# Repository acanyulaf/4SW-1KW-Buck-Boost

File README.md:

# 4SW-1KW-Buck-Boost
 1kW 28V 4 Switches Buck Boost Converter with 28V Fixed Output, Voltage Ripple<1% Inductor Current Ripple<30%

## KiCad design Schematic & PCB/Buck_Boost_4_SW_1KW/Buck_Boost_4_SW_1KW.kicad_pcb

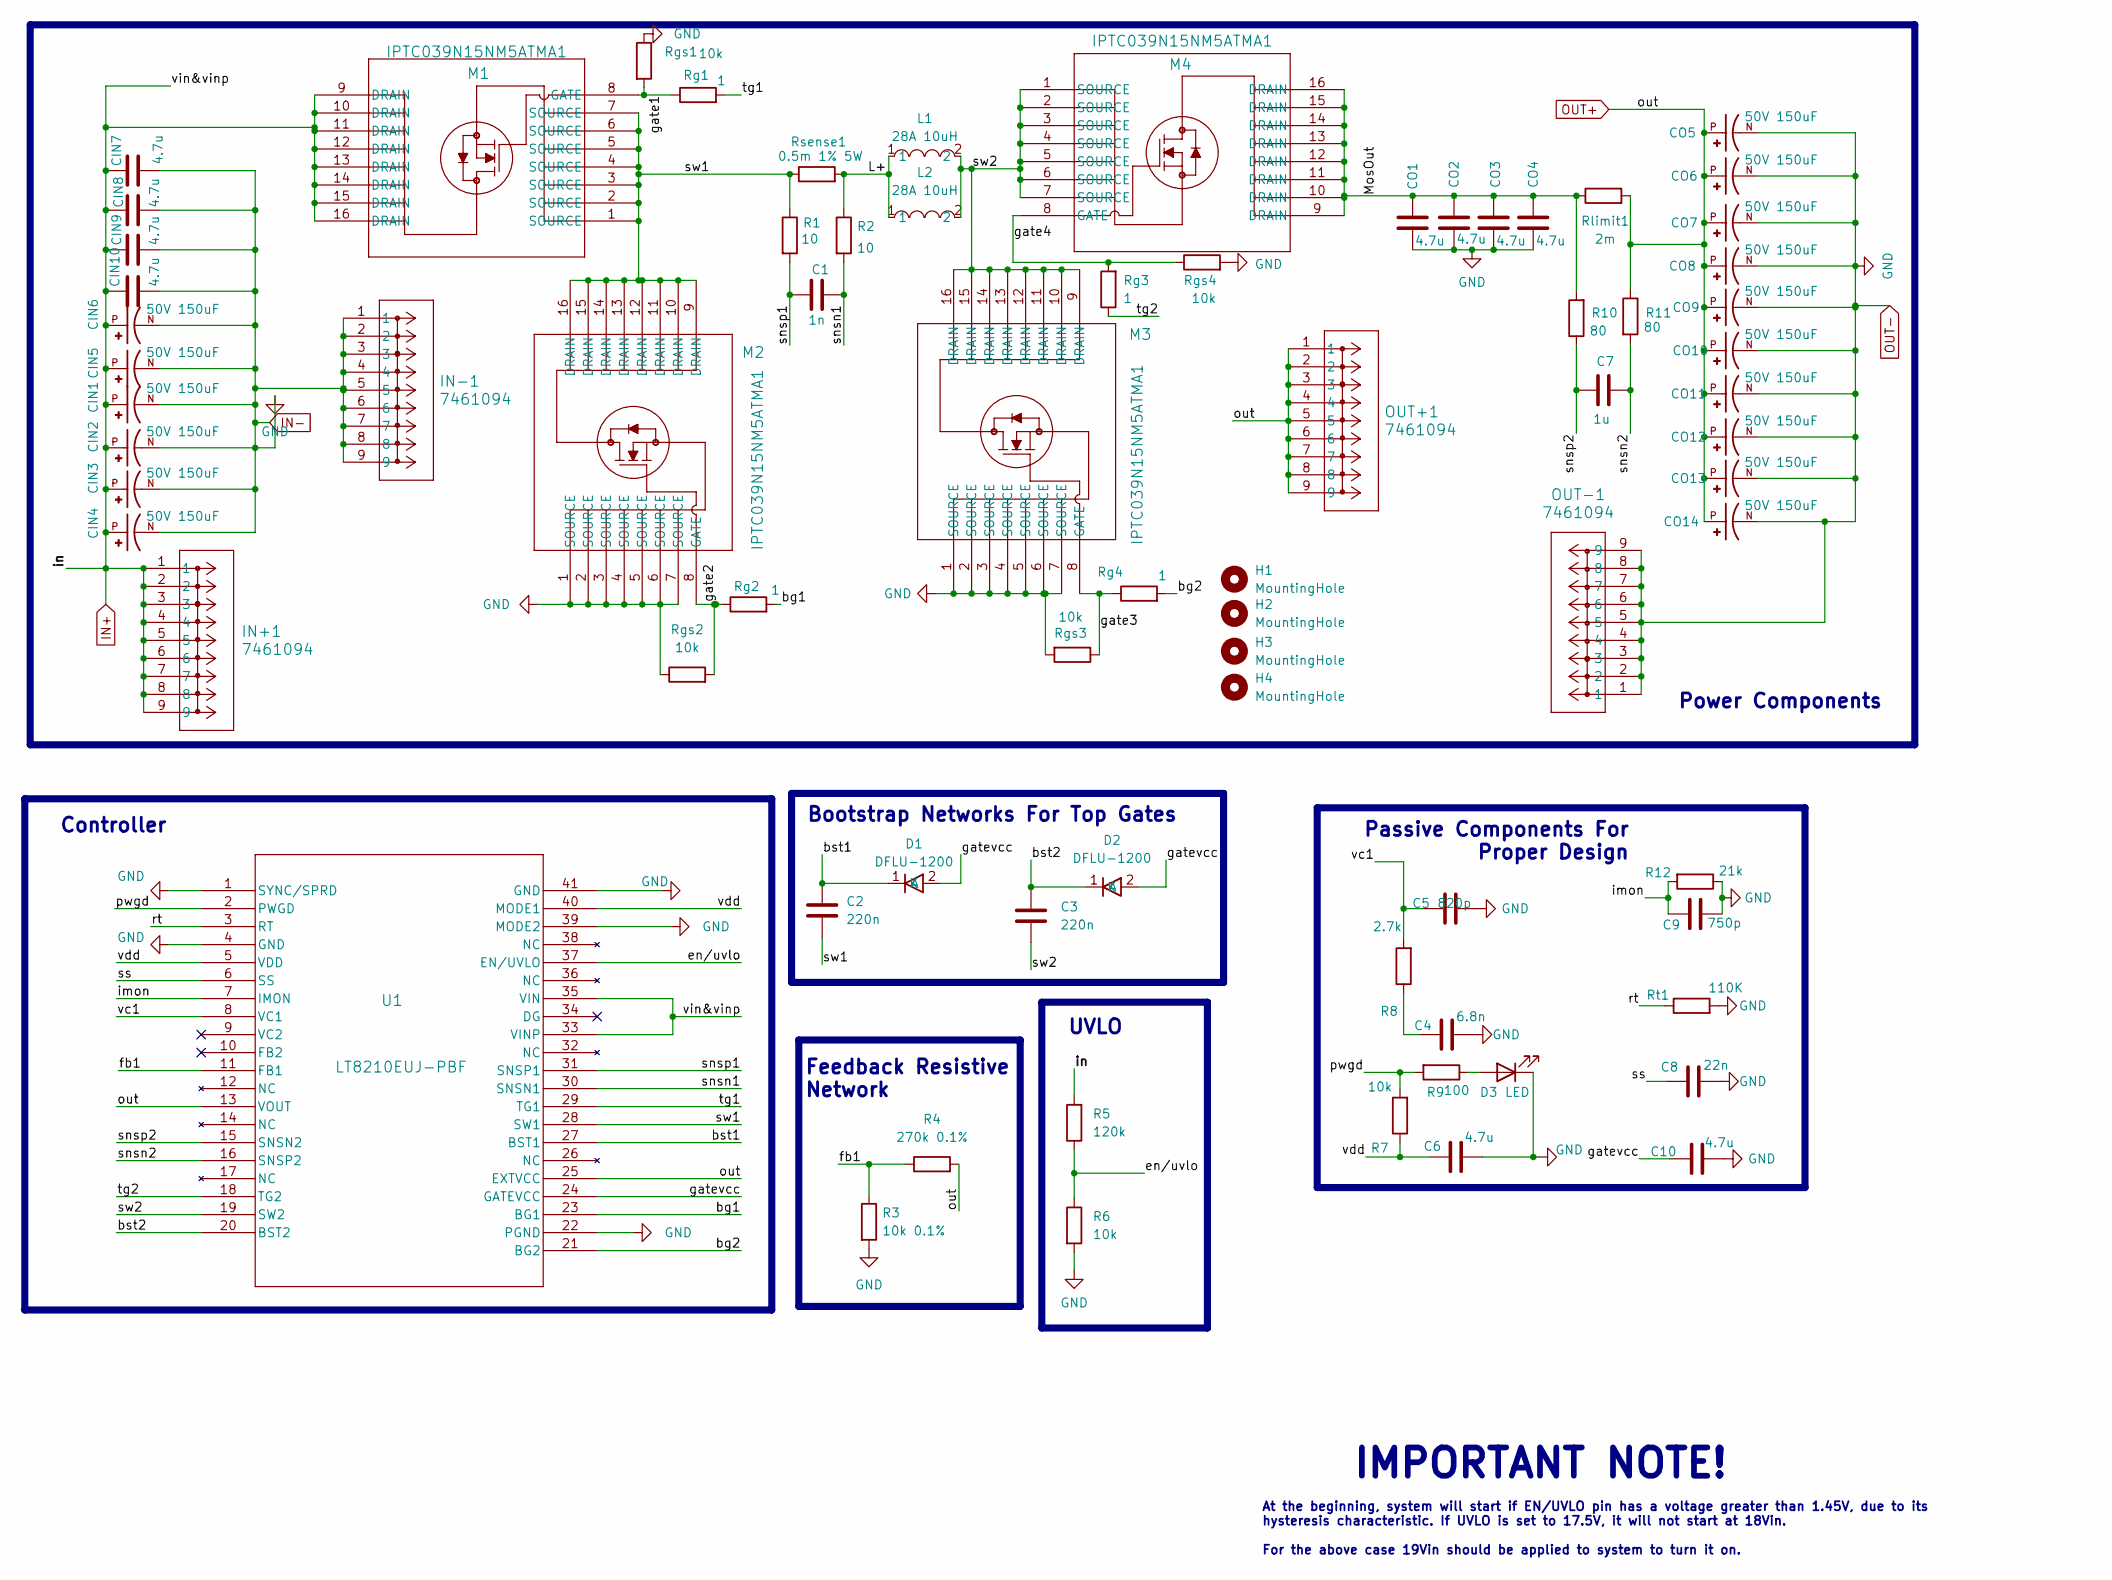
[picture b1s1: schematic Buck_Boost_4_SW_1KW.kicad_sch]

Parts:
C1: 1n; C_0603_1608Metric
C2, C3: 220n; C_0603_1608Metric
C4: 6.8n; C_0603_1608Metric
C5: 820p; C_0603_1608Metric
C6, C10: 4.7u; C_0805_2012Metric
C7: 1u; C_0603_1608Metric
C8: 22n; C_0603_1608Metric
C9: 750p; C_0603_1608Metric
CIN1, CIN2, CIN3, CIN4, CIN5, CIN6: 50V 150uF; EEH-AZS1H151B; PARTREV 30-SEP-20
CIN7, CIN8, CIN9, CIN10: 4.7u; C_0805_2012Metric
CO1, CO2, CO3, CO4: 4.7u; C_0805_2012Metric
CO5, CO6, CO7, CO8, CO9, CO10, CO11, CO12, CO13, CO14: 50V 150uF; EEH-AZS1H151B; PARTREV 30-SEP-20
D1, D2: DFLU-1200; D_PowerDI-123
D3: LED; LED_0603_1608Metric
H1, H2, H3, H4: MountingHole; MountingHole_3mm
IN+1: 7461094; Würth RedCube Terminals-7461094
IN-1: 7461094; Würth RedCube Terminals-7461094
L1, L2: 28A 10uH; IHLP8787MZER100M51
M1, M2, M3, M4: IPTC039N15NM5ATMA1; PG-HDSOP-16-2
OUT+1: 7461094; Würth RedCube Terminals-7461094
OUT-1: 7461094; Würth RedCube Terminals-7461094
R1, R2: 10; R_0603_1608Metric
R3: 10k 0.1%; R_0603_1608Metric
R4: 270k 0.1%; R_0603_1608Metric
R5: 120k; R_0603_1608Metric
R6, R7: 10k; R_0603_1608Metric
R8: 2.7k; R_0603_1608Metric
R9: 100; R_0603_1608Metric
R10, R11: 80; R_0603_1608Metric
R12: 21k; R_0603_1608Metric
Rg1, Rg2, Rg3, Rg4: 1; R_1206_3216Metric
Rgs1, Rgs2, Rgs3, Rgs4: 10k; R_0603_1608Metric
Rlimit1: 2m; R_2512_6332Metric
Rsense1: 0.5m 1% 5W; R_2512_6332Metric
Rt1: 110K; R_0603_1608Metric
U1: LT8210EUJ-PBF; PQFN40_UJ_ADI

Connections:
/L+: L1.1, L2.1, R2.1, Rsense1.2
/MosOut: CO1.1, CO2.1, CO3.1, CO4.1, M4.9 (DRAIN), M4.10 (DRAIN), M4.11 (DRAIN), M4.12 (DRAIN), M4.13 (DRAIN), M4.14 (DRAIN), M4.15 (DRAIN), M4.16 (DRAIN), R10.2, Rlimit1.1
/bg1: Rg2.2, U1.23 (BG1)
/bg2: Rg4.2, U1.21 (BG2)
/bst1: C2.1, D1.1 (K), U1.27 (BST1)
/bst2: C3.1, D2.1 (K), U1.20 (BST2)
/en/uvlo: R5.1, R6.1, U1.37 (EN/UVLO)
/fb1: R3.1, R4.1, U1.11 (FB1)
/gate1: M1.8 (GATE), Rg1.1, Rgs1.2
/gate2: M2.8 (GATE), Rg2.1, Rgs2.2
/gate3: M3.8 (GATE), Rg4.1, Rgs3.1
/gate4: M4.8 (GATE), Rg3.2, Rgs4.1
/gatevcc: C10.1, D1.2 (A), D2.2 (A), U1.24 (GATEVCC)
/imon: C9.1, R12.2, U1.7 (IMON)
/pwgd: R7.2, R9.2, U1.2 (PWGD)
/rt: Rt1.1, U1.3 (RT)
/snsn1: C1.2, R2.2, U1.30 (SNSN1)
/snsn2: C7.2, R11.2, U1.16 (SNSP2)
/snsp1: C1.1, R1.2, U1.31 (SNSP1)
/snsp2: C7.1, R10.1, U1.15 (SNSN2)
/ss: C8.1, U1.6 (SS)
/sw1: C2.2, M1.1 (SOURCE), M1.2 (SOURCE), M1.3 (SOURCE), M1.4 (SOURCE), M1.5 (SOURCE), M1.6 (SOURCE), M1.7 (SOURCE), M2.9 (DRAIN), M2.10 (DRAIN), M2.11 (DRAIN), M2.12 (DRAIN), M2.13 (DRAIN), M2.14 (DRAIN), M2.15 (DRAIN), M2.16 (DRAIN), R1.1, Rsense1.1, U1.28 (SW1)
/sw2: C3.2, L1.2, L2.2, M3.9 (DRAIN), M3.10 (DRAIN), M3.11 (DRAIN), M3.12 (DRAIN), M3.13 (DRAIN), M3.14 (DRAIN), M3.15 (DRAIN), M3.16 (DRAIN), M4.1 (SOURCE), M4.2 (SOURCE), M4.3 (SOURCE), M4.4 (SOURCE), M4.5 (SOURCE), M4.6 (SOURCE), M4.7 (SOURCE), U1.19 (SW2)
/tg1: Rg1.2, U1.29 (TG1)
/tg2: Rg3.1, U1.18 (TG2)
/vc1: C5.1, R8.2, U1.8 (VC1)
/vdd: C6.2, R7.1, U1.5 (VDD), U1.40 (MODE1)
IN+: CIN1.P, CIN2.P, CIN3.P, CIN4.P, CIN5.P, CIN6.P, CIN7.1, CIN8.1, CIN9.1, CIN10.1, IN+1.1, IN+1.2, IN+1.3, IN+1.4, IN+1.5, IN+1.6, IN+1.7, IN+1.8, IN+1.9, M1.9 (DRAIN), M1.10 (DRAIN), M1.11 (DRAIN), M1.12 (DRAIN), M1.13 (DRAIN), M1.14 (DRAIN), M1.15 (DRAIN), M1.16 (DRAIN), R5.2, U1.33 (VINP), U1.35 (VIN)
IN-: C4.2, C5.2, C6.1, C8.2, C9.2, C10.2, CIN1.N, CIN2.N, CIN3.N, CIN4.N, CIN5.N, CIN6.N, CIN7.2, CIN8.2, CIN9.2, CIN10.2, CO1.2, CO2.2, CO3.2, CO4.2, CO5.N, CO6.N, CO7.N, CO8.N, CO9.N, CO10.N, CO11.N, CO12.N, CO13.N, CO14.N, D3.1 (K), IN-1.1, IN-1.2, IN-1.3, IN-1.4, IN-1.5, IN-1.6, IN-1.7, IN-1.8, IN-1.9, M2.1 (SOURCE), M2.2 (SOURCE), M2.3 (SOURCE), M2.4 (SOURCE), M2.5 (SOURCE), M2.6 (SOURCE), M2.7 (SOURCE), M3.1 (SOURCE), M3.2 (SOURCE), M3.3 (SOURCE), M3.4 (SOURCE), M3.5 (SOURCE), M3.6 (SOURCE), M3.7 (SOURCE), OUT-1.1, OUT-1.2, OUT-1.3, OUT-1.4, OUT-1.5, OUT-1.6, OUT-1.7, OUT-1.8, OUT-1.9, R3.2, R6.2, R12.1, Rgs1.1, Rgs2.1, Rgs3.2, Rgs4.2, Rt1.2, U1.1 (SYNC/SPRD), U1.4 (GND), U1.22 (PGND), U1.39 (MODE2), U1.41 (GND)
unnamed: C4.1, R8.1
unnamed: D3.2 (A), R9.1
OUT+: CO5.P, CO6.P, CO7.P, CO8.P, CO9.P, CO10.P, CO11.P, CO12.P, CO13.P, CO14.P, OUT+1.1, OUT+1.2, OUT+1.3, OUT+1.4, OUT+1.5, OUT+1.6, OUT+1.7, OUT+1.8, OUT+1.9, R4.2, R11.1, Rlimit1.2, U1.13 (VOUT), U1.25 (EXTVCC)

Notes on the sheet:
Controller
Bootstrap Networks For Top Gates
UVLO
At the beginning, system will start if EN/UVLO pin has a voltage greater than 1.45V, due to its hysteresis characteristic. If UVLO is set to 17.5V, it will not start at 18Vin. For the above case 19Vin should be applied to system to turn it on.
Power Components
Passive Components For Proper Design
IMPORTANT NOTE!
Feedback Resistive Network

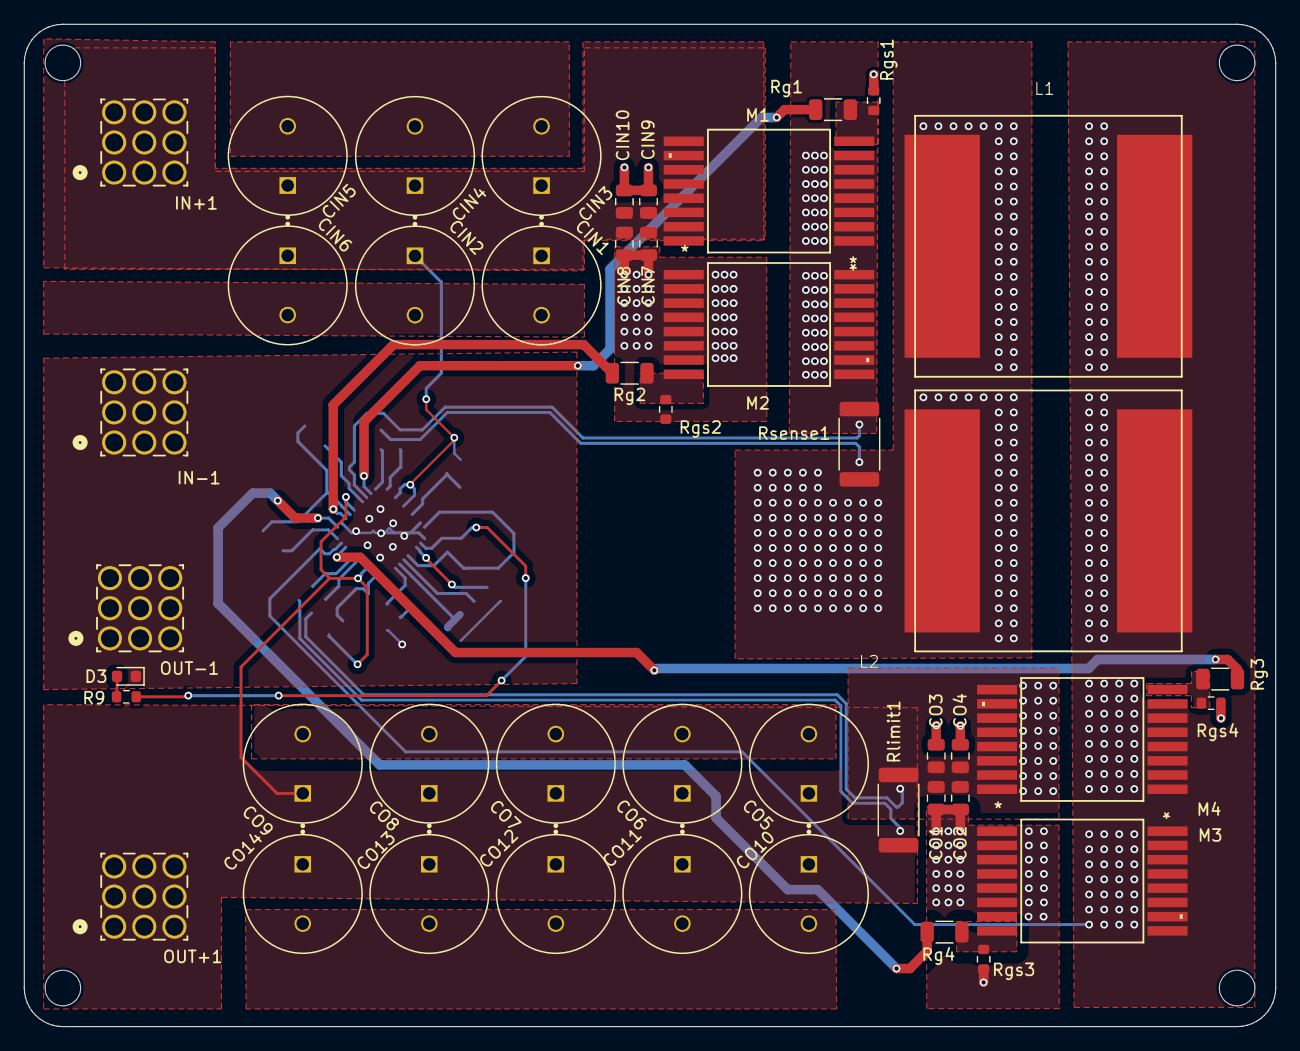
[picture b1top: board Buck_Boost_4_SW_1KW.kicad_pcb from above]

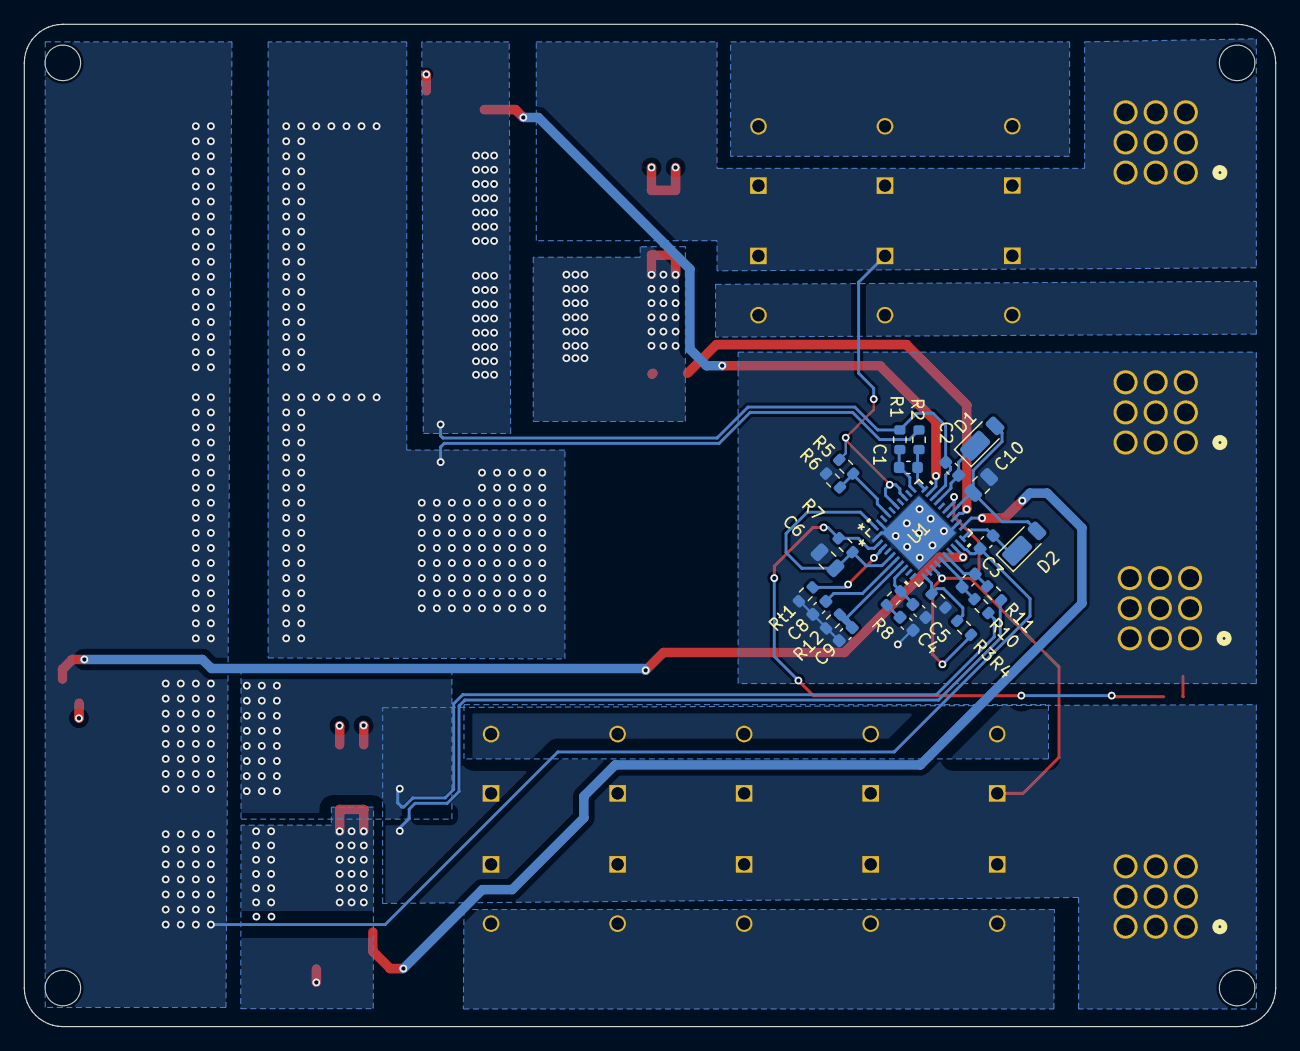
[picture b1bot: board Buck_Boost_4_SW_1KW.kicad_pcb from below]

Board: 4 copper layers, 105.5 x 84.5 mm, 75 parts (25 on the bottom side), 32 nets.
